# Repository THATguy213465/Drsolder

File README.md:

# Drsolder
Dr House

Slack User:
THATguy

Collaboration with:
egg_splats and
Sewer Gar

Description:
This is my first board, I used Dr. House and my cat named Winston.

List of materials:
Battery Cell,
3 20 ohm resistors,
2 leds,
6mm push button,
Motor,
and a potentiometer.

Pictures:

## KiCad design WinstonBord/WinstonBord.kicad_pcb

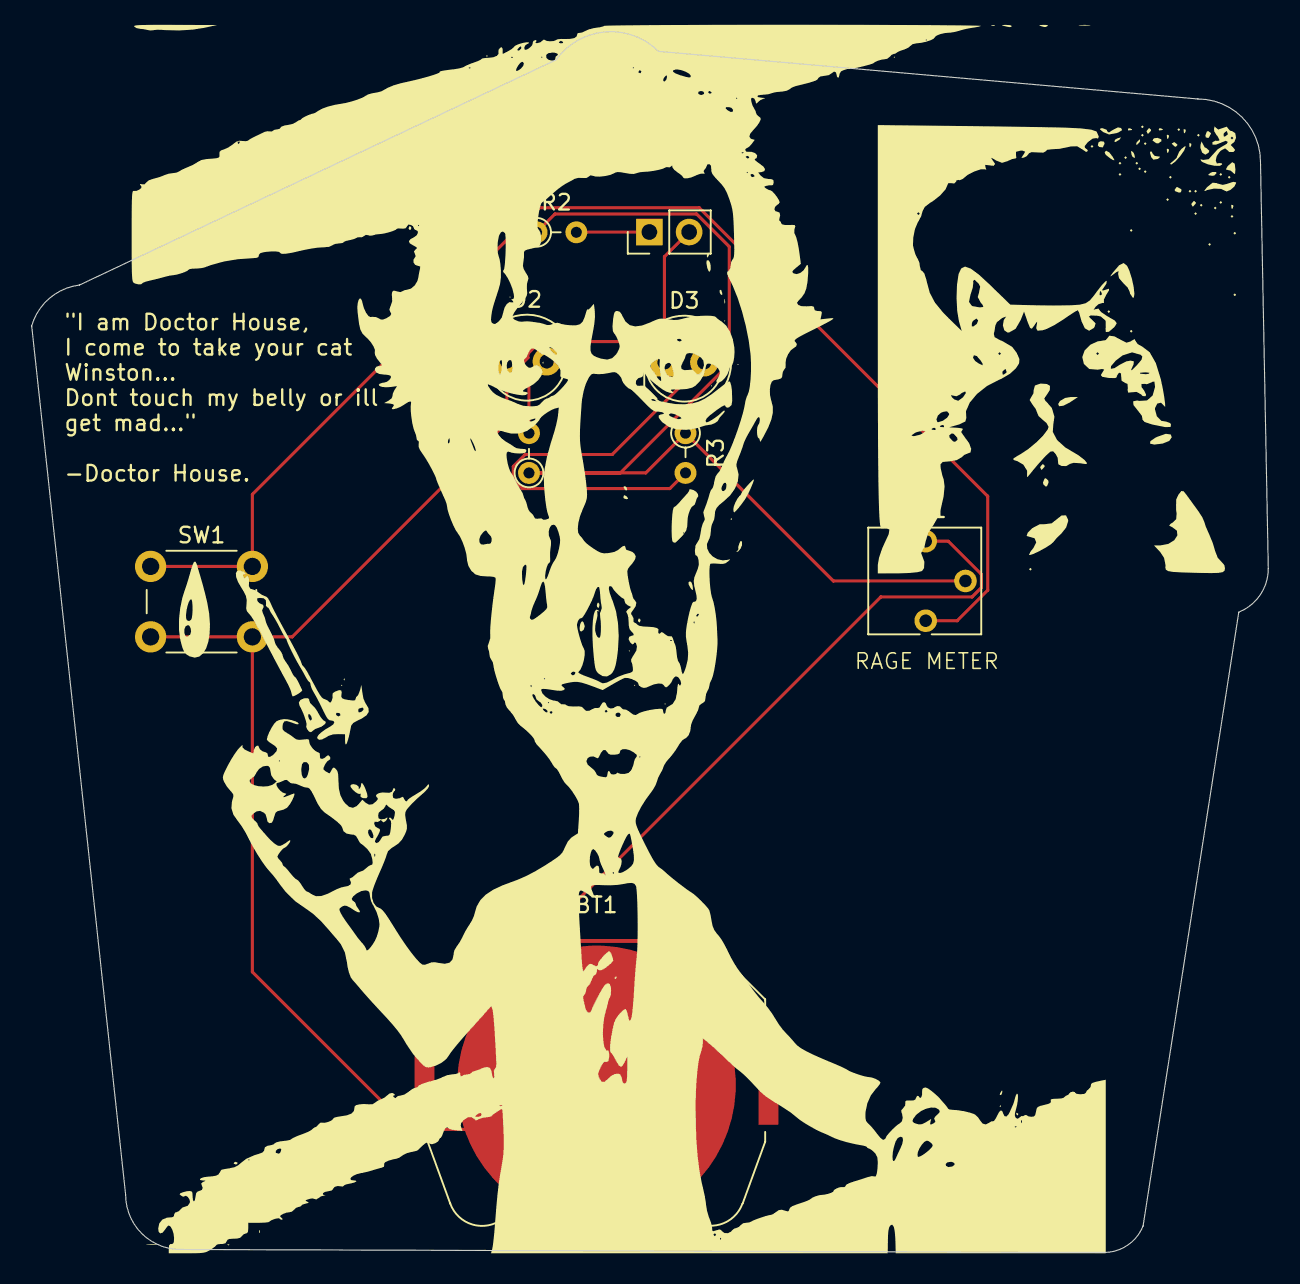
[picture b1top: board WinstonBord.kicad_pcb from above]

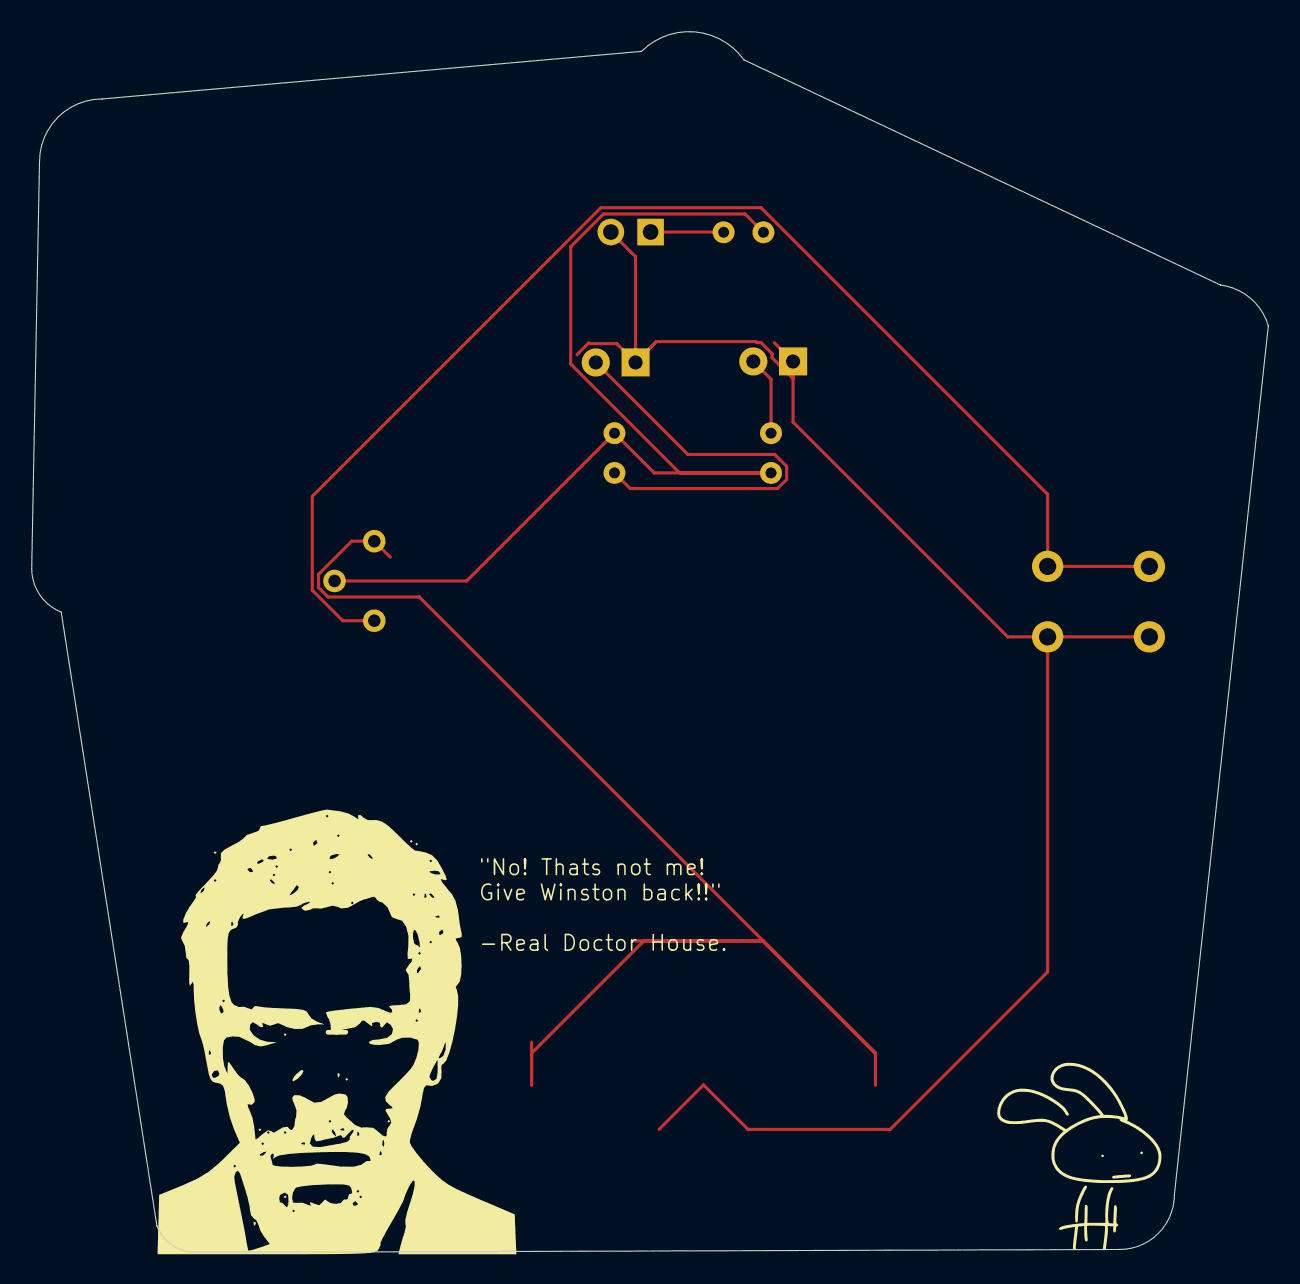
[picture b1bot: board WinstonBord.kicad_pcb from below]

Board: 2 copper layers, 79.0 x 78.0 mm, 13 parts (2 on the bottom side), 7 nets.

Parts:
 : LOGO
 #2,  #3: LOGO
-: LOGO
BT1: Battery_Cell; BatteryHolder_Keystone_3034_1x20mm
D2, D3: LED; LED_D5.0mm
M1: Motor_DC; PinHeader_1x02_P2.54mm_Vertical
R1, R2, R3: R; R_Axial_DIN0204_L3.6mm_D1.6mm_P2.54mm_Vertical
RV1: Potentiometer_Vishay_T73YP_Vertical
SW1: SW_Push; SW_PUSH_6mm

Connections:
unnamed: BT1.1 (+), RV1.3
unnamed: BT1.2 (-), D2.1 (K), D3.1 (K), M1.2 (-), SW1.2
unnamed: D2.2 (A), R1.2
unnamed: D3.2 (A), R3.2
unnamed: M1.1 (+), R2.2
unnamed: R1.1, R2.1, R3.1, RV1.2
unnamed: RV1.1, SW1.1

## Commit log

2025-05-02 README.md
    READREADREAD
2025-05-03 README.md
